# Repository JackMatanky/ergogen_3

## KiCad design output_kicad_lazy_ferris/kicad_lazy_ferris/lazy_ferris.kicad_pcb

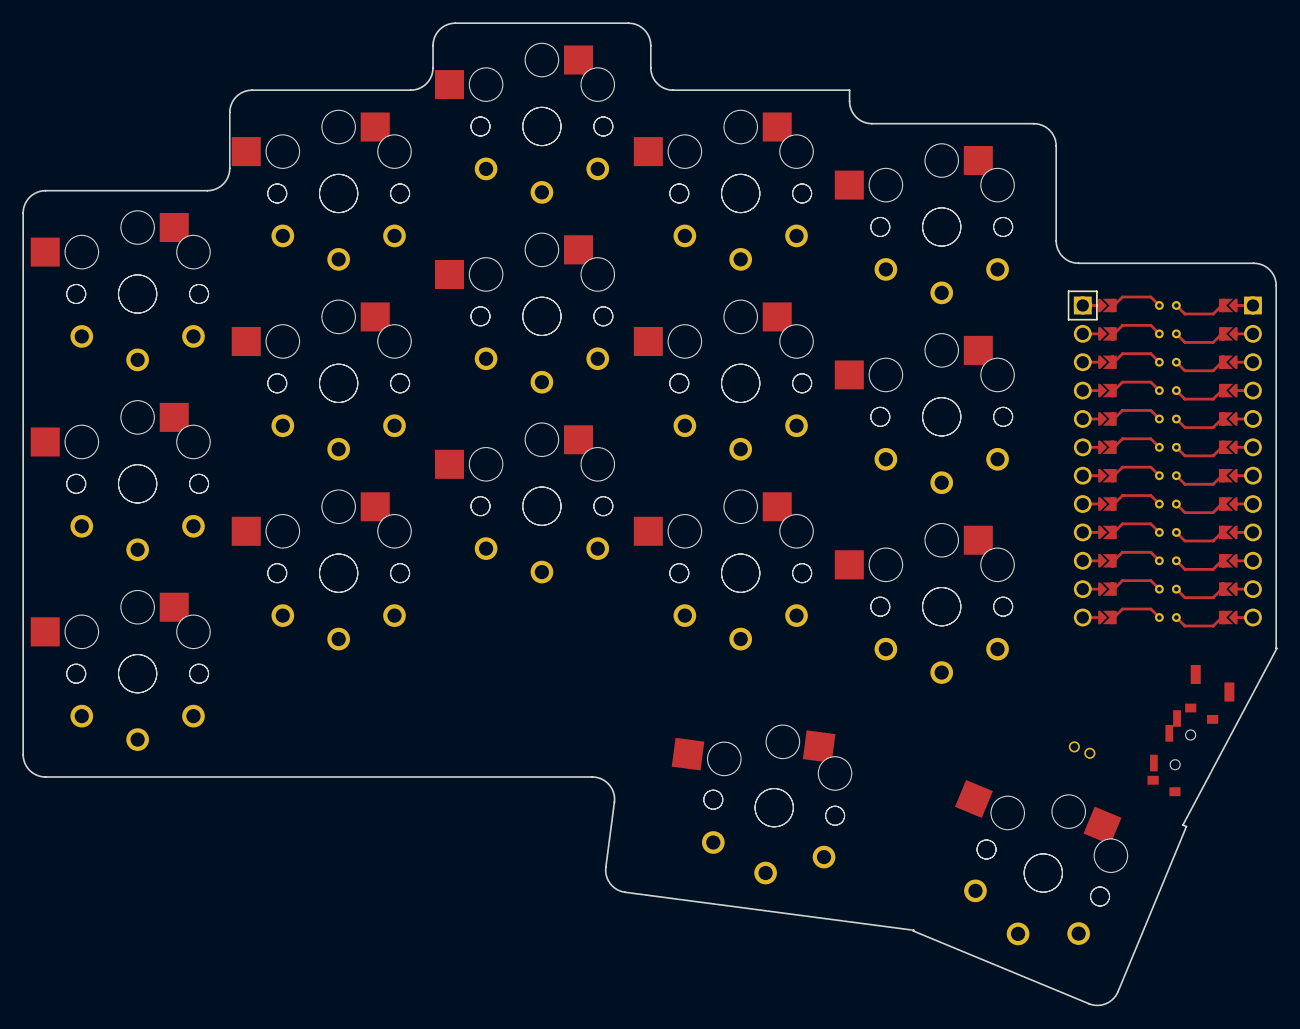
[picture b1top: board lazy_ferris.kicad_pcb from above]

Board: 2 copper layers, 112.3 x 88.0 mm, 35 parts (0 on the bottom side), 18 nets, no tracks yet.

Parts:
MCU1: ProMicro
S1, S2, S3, S4, S5, S6, S7, S8, S9, S10, S11, S12, S13, S14, S15, S16, S17, S18, S19, S20, S21, S22, S23, S24, S25, S26, S27, S28, S29, S30, S31, S32, S33, S34: PG1350

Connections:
GND: MCU1.2, MCU1.21, MCU1.22, S1.2, S2.2, S3.2, S4.2, S5.2, S6.2, S7.2, S8.2, S9.2, S10.2, S11.2, S12.2, S13.2, S14.2, S15.2, S16.2, S17.2, S18.2, S19.2, S20.2, S21.2, S22.2, S23.2, S24.2, S25.2, S26.2, S27.2, S28.2, S29.2, S30.2, S31.2, S32.2, S33.2, S34.2
P0: MCU1.23, S17.1, S18.1
P1: MCU1.24, S29.1, S30.1
P2: MCU1.20, S5.1, S6.1
P3: MCU1.19, S27.1, S28.1
P4: MCU1.18, S15.1, S16.1
P5: MCU1.17, S3.1, S4.1
P6: MCU1.16, S25.1, S26.1
P7: MCU1.15, S13.1, S14.1
P8: MCU1.14, S1.1, S2.1
P9: MCU1.13, S31.1, S32.1
P10: MCU1.12, S33.1, S34.1
P14: MCU1.10, S7.1, S8.1
P15: MCU1.9, S19.1, S20.1
P18: MCU1.8, S9.1, S10.1
P19: MCU1.7, S21.1, S22.1
P20: MCU1.6, S11.1, S12.1
P21: MCU1.5, S23.1, S24.1

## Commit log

2022-12-20 commit -m
2023-01-03 add all current computer files to github
2023-01-10 Reorganizing keyboard dev files
2023-01-13 final commit of ergogen v3
